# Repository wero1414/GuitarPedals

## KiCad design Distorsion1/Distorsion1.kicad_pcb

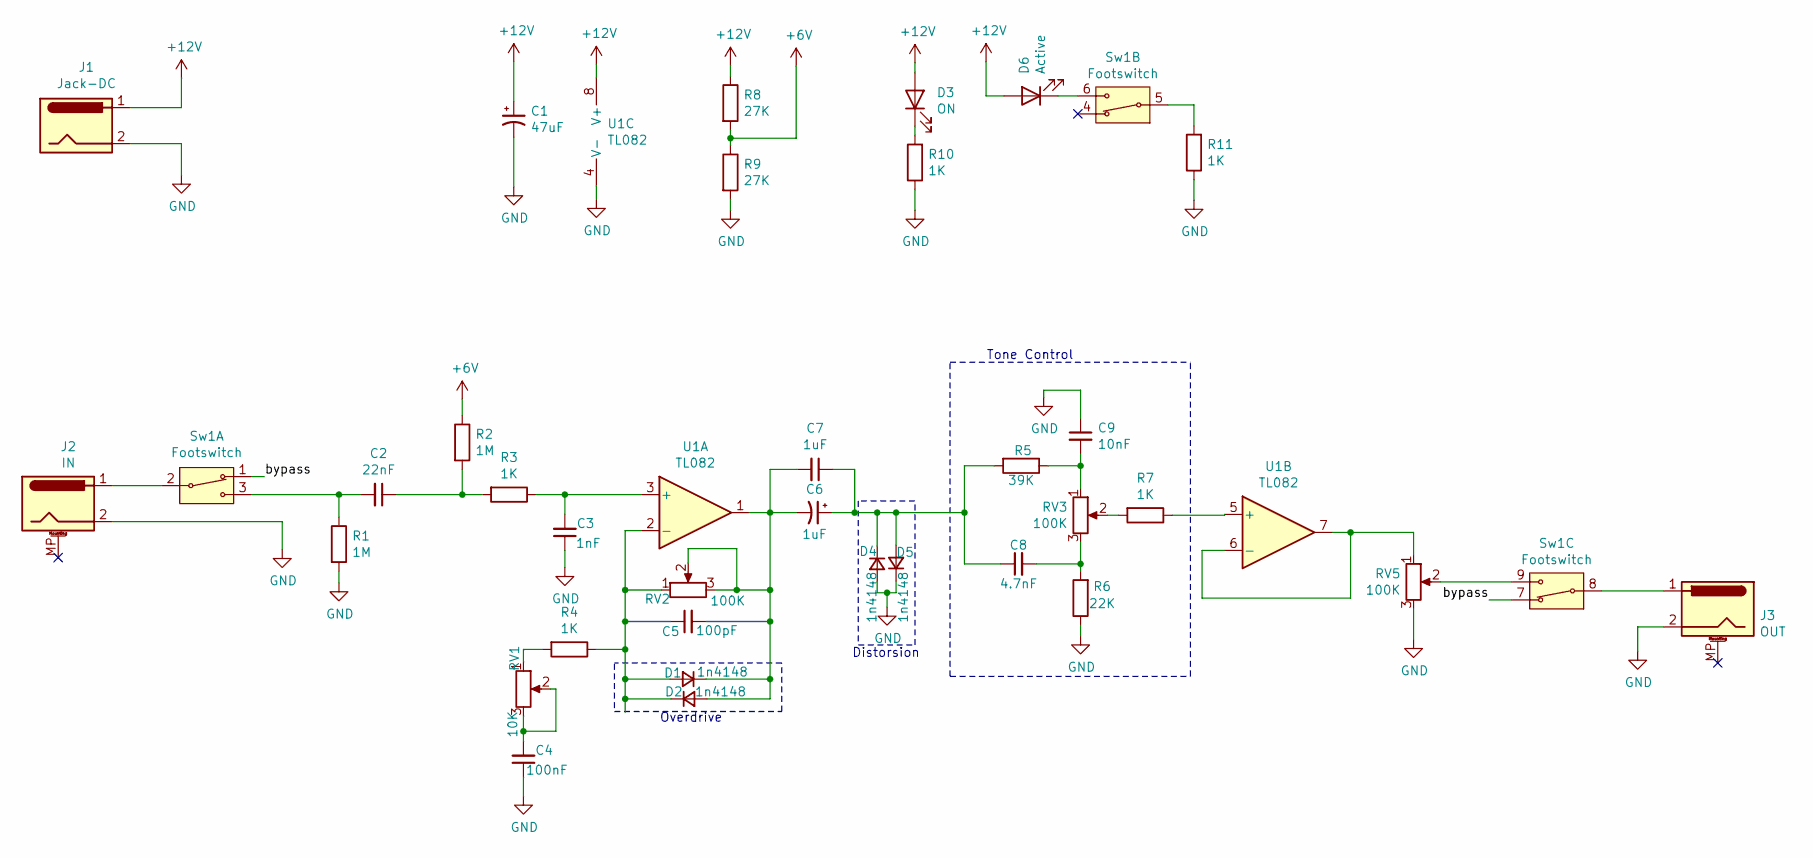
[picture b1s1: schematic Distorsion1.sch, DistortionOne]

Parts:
C1: 47uF; C_0805_2012Metric_Pad1.18x1.45mm_HandSolder
C2: 22nF; C_0805_2012Metric_Pad1.18x1.45mm_HandSolder
C3: 1nF; C_0805_2012Metric_Pad1.18x1.45mm_HandSolder
C4: 100nF; C_0805_2012Metric_Pad1.18x1.45mm_HandSolder
C5: 100pF; C_0805_2012Metric_Pad1.18x1.45mm_HandSolder
C6: 1uF; CP_EIA-3216-18_Kemet-A_Pad1.58x1.35mm_HandSolder
C7: 1uF; C_0805_2012Metric_Pad1.18x1.45mm_HandSolder
C8: 4.7nF; C_0805_2012Metric_Pad1.18x1.45mm_HandSolder
C9: 10nF; C_0805_2012Metric_Pad1.18x1.45mm_HandSolder
D1, D2, D4, D5: 1n4148; D_SOD-523
D3: ON; LED_0805_2012Metric_Pad1.15x1.40mm_HandSolder
D6: Active; LED_0805_2012Metric_Pad1.15x1.40mm_HandSolder
J1: Jack-DC; BarrelJack_CUI_PJ-102AH_Horizontal
J2: IN; NYS2162U
J3: OUT; NYS2162U
R1, R2: 1M; R_0805_2012Metric_Pad1.20x1.40mm_HandSolder
R3, R4, R7, R10, R11: 1K; R_0805_2012Metric_Pad1.20x1.40mm_HandSolder
R5: 39K; R_0805_2012Metric_Pad1.20x1.40mm_HandSolder
R6: 22K; R_0805_2012Metric_Pad1.20x1.40mm_HandSolder
R8, R9: 27K; R_0805_2012Metric_Pad1.20x1.40mm_HandSolder
RV1: 10K; PinSocket_1x03_P2.54mm_Vertical
RV2, RV3, RV5: 100K; PinSocket_1x03_P2.54mm_Vertical
Sw1: Footswitch; FS57003PLT2B2M2QE
U1: TL082; TSSOP-8_4.4x3mm_P0.65mm

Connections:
+6V: R2.1, R8.2, R9.1
+12V: C1.1, D3.2 (A), D6.2 (A), J1.1, R8.1, U1.8 (V+)
/bypass: Sw1.1, Sw1.7
GND: C1.2, C3.1, C4.1, C9.1, D4.2 (A), D5.1 (K), J1.2, J2.2, J3.2, R1.2, R6.1, R9.2, R10.1, R11.1, RV5.3, U1.4 (V-)
unnamed: C2.1, R2.2, R3.2
unnamed: C2.2, R1.1, Sw1.3
unnamed: C3.2, R3.1, U1.3 (+)
unnamed: C4.2, RV1.2, RV1.3
unnamed: C5.1, D1.2 (A), D2.1 (K), R4.1, RV2.1, U1.2 (-)
unnamed: C5.2, C6.2, C7.2, D1.1 (K), D2.2 (A), RV2.2, RV2.3, U1.1
unnamed: C6.1, C7.1, C8.1, D4.1 (K), D5.2 (A), R5.2
unnamed: C8.2, R6.2, RV3.3
unnamed: C9.2, R5.1, RV3.1
unnamed: D3.1 (K), R10.2
unnamed: D6.1 (K), Sw1.6
unnamed: J2.1, Sw1.2
unnamed: J3.1, Sw1.8
unnamed: R4.2, RV1.1
unnamed: R7.1, U1.5 (+)
unnamed: R7.2, RV3.2
unnamed: R11.2, Sw1.5
unnamed: RV5.1, U1.6 (-), U1.7
unnamed: RV5.2, Sw1.9

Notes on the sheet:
Tone Control
Distorsion
Overdrive

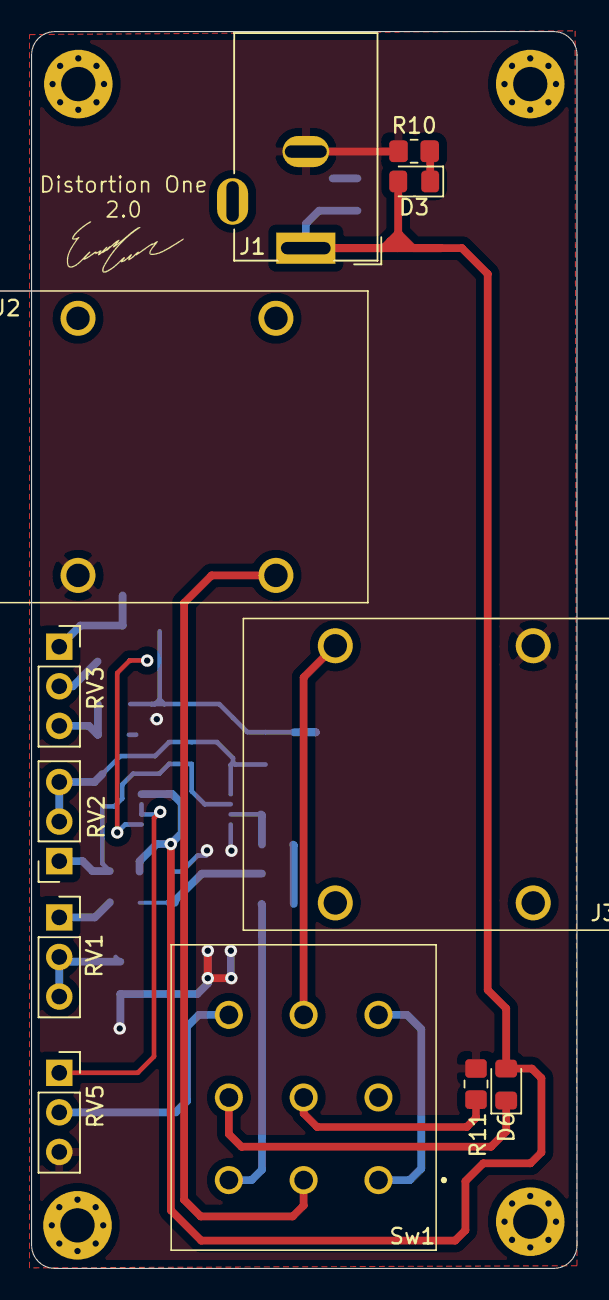
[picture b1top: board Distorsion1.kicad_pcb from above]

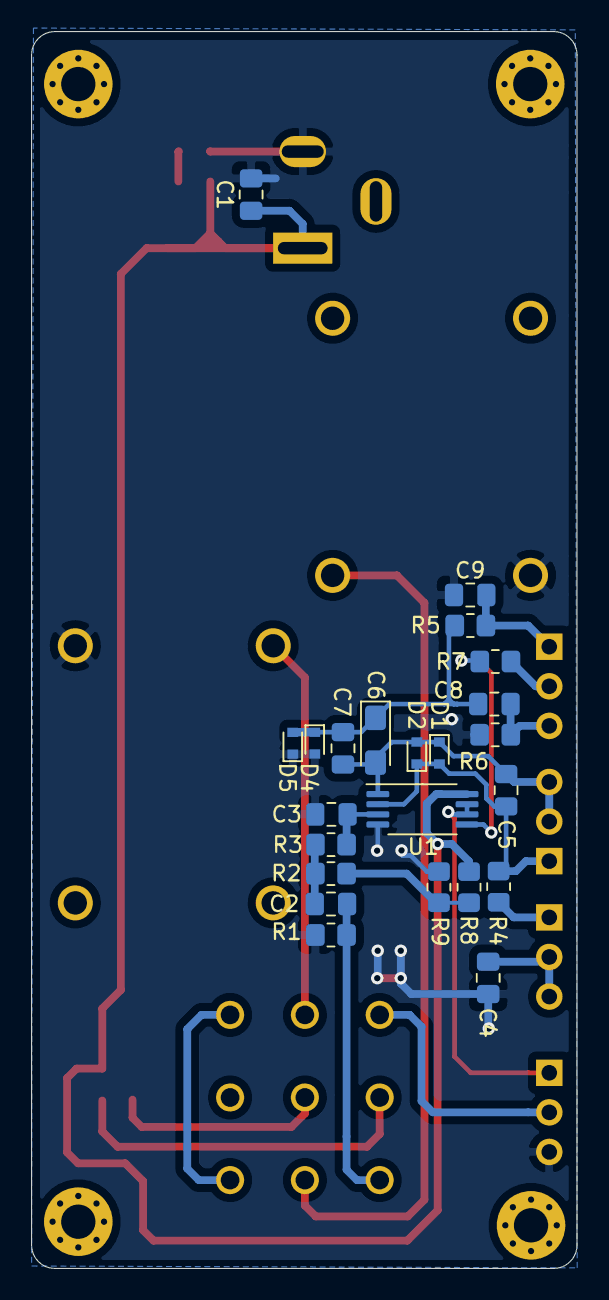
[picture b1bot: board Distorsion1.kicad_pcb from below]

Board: 2 copper layers, 35.0 x 79.4 mm, 35 parts (23 on the bottom side), 23 nets.

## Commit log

2020-11-10 add distorsion1
2020-11-28 Update 1.1- cambio de isteresis y buffer (esquematico)
2020-11-28 Add local library
2021-06-11 PCB 1.0
2021-06-12 PCB1.1(Aumento de pistas de 0.2 a 0.5)
2021-06-12 PCB1.2(Cambio lugar de pot)
2021-06-24 PCB2.0 Nuevo diseño
2021-06-28 PCB2.0(cambio de pocicion de jacks y circuito mas cerca de la señal)
2021-06-28 PCB2.0(cambio de parte mecanica y circuito mas cerca de la señal)
2021-06-28 PCB 2.0.1 (añadido de tierra)
2021-06-30 update traces
2021-07-01 jacks cacados 1 cm
